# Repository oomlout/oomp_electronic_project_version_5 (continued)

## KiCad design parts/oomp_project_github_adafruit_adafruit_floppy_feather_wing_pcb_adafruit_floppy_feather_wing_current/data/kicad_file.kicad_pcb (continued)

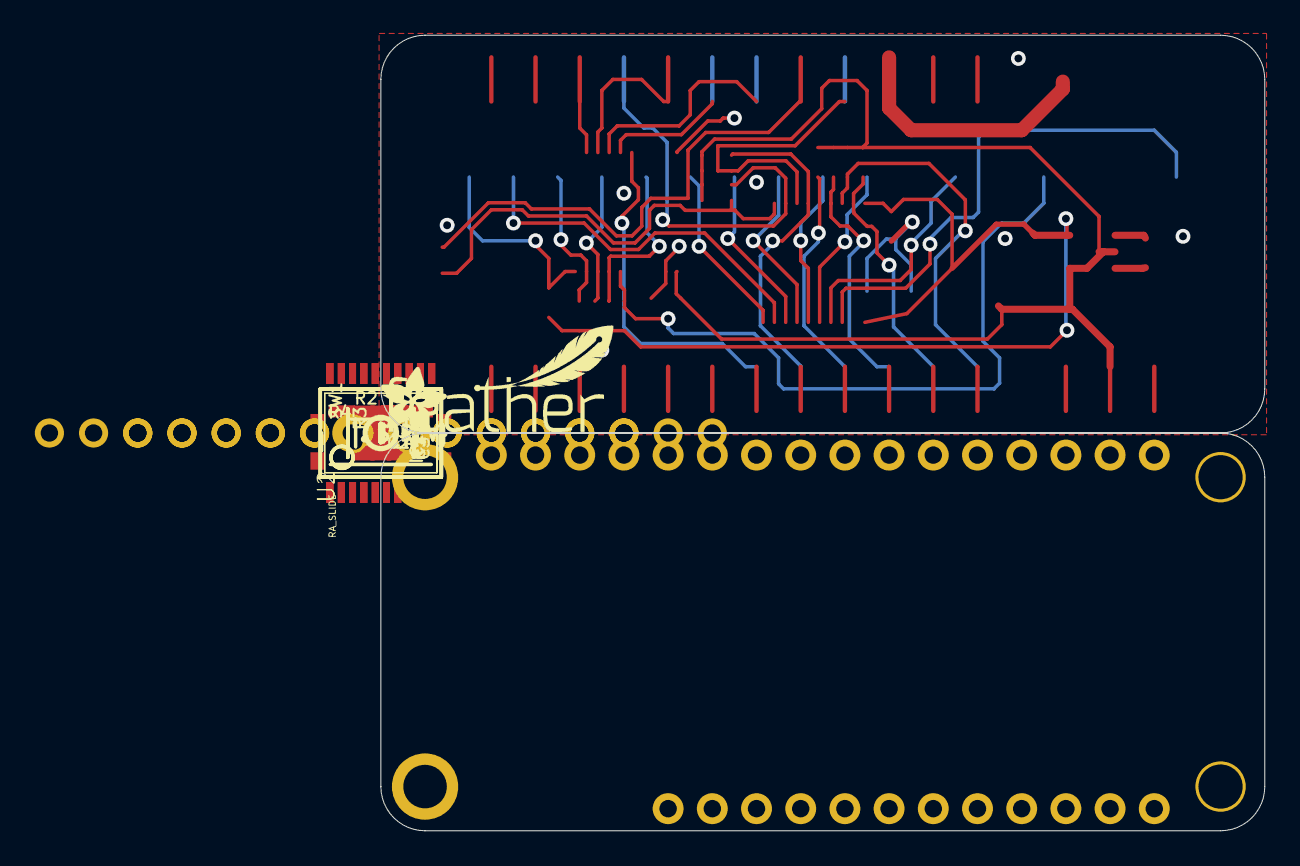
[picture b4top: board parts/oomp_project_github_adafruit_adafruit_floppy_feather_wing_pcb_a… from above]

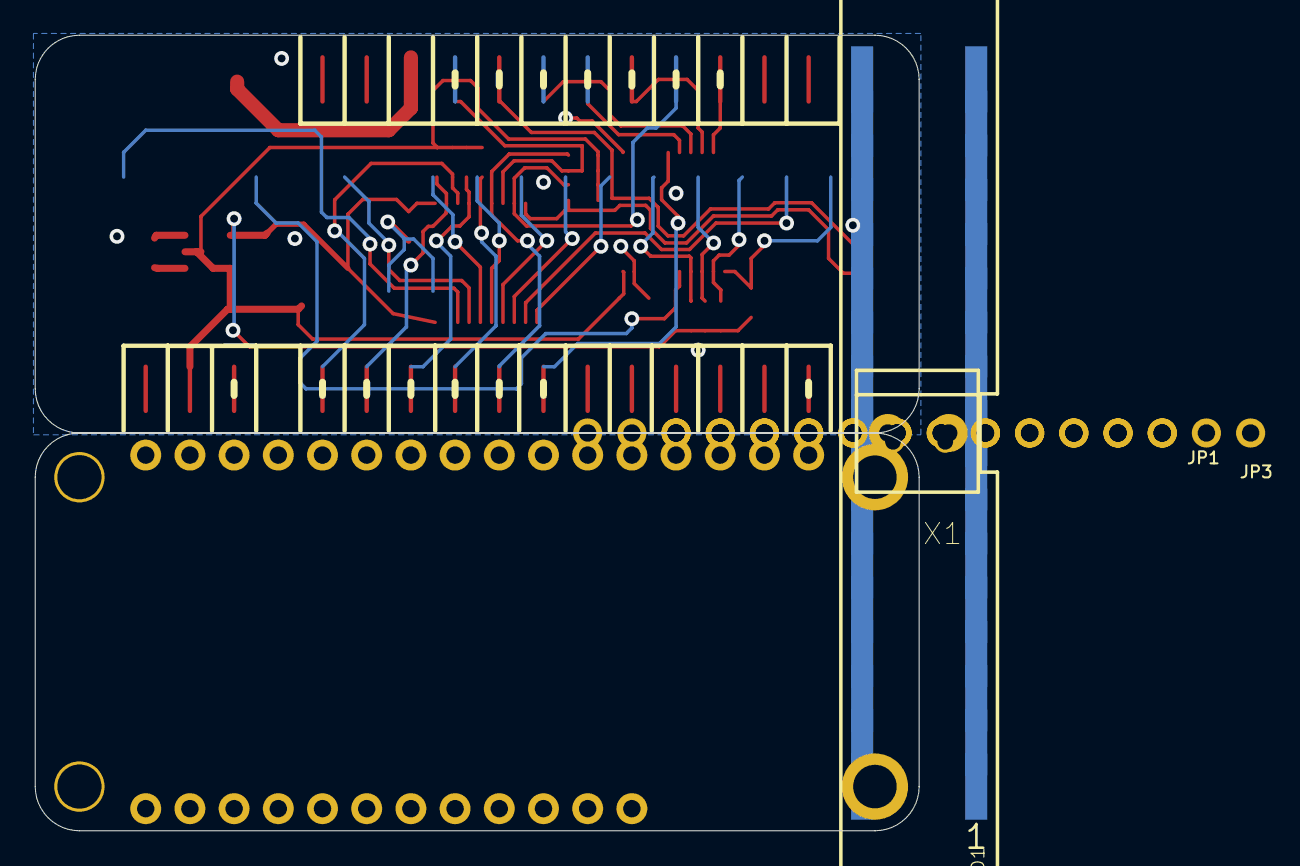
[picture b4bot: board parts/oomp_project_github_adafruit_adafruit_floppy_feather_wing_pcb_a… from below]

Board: 2 copper layers, 50.8 x 45.7 mm, 59 parts (26 on the bottom side), 45 nets.

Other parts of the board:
PLABEL0: PLABEL0
PLABEL1: PLABEL1
PLABEL2: PLABEL2
PLABEL3: PLABEL3
PLABEL4: PLABEL4
PLABEL5: PLABEL5
PLABEL6: PLABEL6
PLABEL7: PLABEL7
PLABEL8: PLABEL8
PLABEL9: PLABEL9
PLABEL10: PLABEL10
PLABEL11: PLABEL11
PLABEL12: PLABEL12
PLABEL13: PLABEL13
PLABEL14: PLABEL14
PLABEL15: PLABEL15
PLABEL16: PLABEL16
PLABEL17: PLABEL17
PLABEL18: PLABEL18
PLABEL19: PLABEL19
PLABEL20: PLABEL20
PLABEL21: PLABEL21
PLABEL22: PLABEL22
PLABEL23: PLABEL23
PLABEL24: PLABEL24
PLABEL25: PLABEL25
PLABEL26: PLABEL26
PLABEL27: PLABEL27
PLABEL28: PLABEL28
PLABEL29: PLABEL29
PLABEL30: PLABEL30
PLABEL31: PLABEL31
PLABEL32: PLABEL32
PLABEL33: PLABEL33
PLABEL34: PLABEL34
PLABEL35: PLABEL35
U$26: PCBFEAT-REV-040
U$27: FEATHERLOGO_SMALL
U$28: ADAFRUIT_3.5MM

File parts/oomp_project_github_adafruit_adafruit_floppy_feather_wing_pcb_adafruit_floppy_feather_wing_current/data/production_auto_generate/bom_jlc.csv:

Comment,Designator,Footprint,LCSC Part #
,JP1,Adafruit Floppy FeatherWing-import-fps:1X12_ROUND,C7501588
,JP3,Adafruit Floppy FeatherWing-import-fps:1X16_ROUND,C7501270
,U$28,Adafruit Floppy FeatherWing-import-fps:ADAFRUIT_3.5MM,
,U$27,Adafruit Floppy FeatherWing-import-fps:FEATHERLOGO_SMALL,
,U$26,Adafruit Floppy FeatherWing-import-fps:PCBFEAT-REV-040,
,PLABEL0,Adafruit Floppy FeatherWing-import-fps:PLABEL0,
,PLABEL1,Adafruit Floppy FeatherWing-import-fps:PLABEL1,
,PLABEL10,Adafruit Floppy FeatherWing-import-fps:PLABEL10,
,PLABEL11,Adafruit Floppy FeatherWing-import-fps:PLABEL11,
,PLABEL12,Adafruit Floppy FeatherWing-import-fps:PLABEL12,
,PLABEL13,Adafruit Floppy FeatherWing-import-fps:PLABEL13,
,PLABEL14,Adafruit Floppy FeatherWing-import-fps:PLABEL14,
,PLABEL15,Adafruit Floppy FeatherWing-import-fps:PLABEL15,
,PLABEL16,Adafruit Floppy FeatherWing-import-fps:PLABEL16,
,PLABEL17,Adafruit Floppy FeatherWing-import-fps:PLABEL17,
,PLABEL18,Adafruit Floppy FeatherWing-import-fps:PLABEL18,
,PLABEL19,Adafruit Floppy FeatherWing-import-fps:PLABEL19,
,PLABEL2,Adafruit Floppy FeatherWing-import-fps:PLABEL2,
,PLABEL20,Adafruit Floppy FeatherWing-import-fps:PLABEL20,
,PLABEL21,Adafruit Floppy FeatherWing-import-fps:PLABEL21,
,PLABEL22,Adafruit Floppy FeatherWing-import-fps:PLABEL22,
,PLABEL23,Adafruit Floppy FeatherWing-import-fps:PLABEL23,
,PLABEL24,Adafruit Floppy FeatherWing-import-fps:PLABEL24,
,PLABEL25,Adafruit Floppy FeatherWing-import-fps:PLABEL25,
,PLABEL26,Adafruit Floppy FeatherWing-import-fps:PLABEL26,
,PLABEL27,Adafruit Floppy FeatherWing-import-fps:PLABEL27,
,PLABEL28,Adafruit Floppy FeatherWing-import-fps:PLABEL28,
,PLABEL29,Adafruit Floppy FeatherWing-import-fps:PLABEL29,
,PLABEL3,Adafruit Floppy FeatherWing-import-fps:PLABEL3,
,PLABEL30,Adafruit Floppy FeatherWing-import-fps:PLABEL30,
,PLABEL31,Adafruit Floppy FeatherWing-import-fps:PLABEL31,
,PLABEL32,Adafruit Floppy FeatherWing-import-fps:PLABEL32,
,PLABEL33,Adafruit Floppy FeatherWing-import-fps:PLABEL33,
,PLABEL34,Adafruit Floppy FeatherWing-import-fps:PLABEL34,
,PLABEL35,Adafruit Floppy FeatherWing-import-fps:PLABEL35,
,PLABEL4,Adafruit Floppy FeatherWing-import-fps:PLABEL4,
,PLABEL5,Adafruit Floppy FeatherWing-import-fps:PLABEL5,
,PLABEL6,Adafruit Floppy FeatherWing-import-fps:PLABEL6,
,PLABEL7,Adafruit Floppy FeatherWing-import-fps:PLABEL7,
,PLABEL8,Adafruit Floppy FeatherWing-import-fps:PLABEL8,
,PLABEL9,Adafruit Floppy FeatherWing-import-fps:PLABEL9,
10uF,"C3,C4",Adafruit Floppy FeatherWing-import-fps:0805-NO,
1uF,"C1,C2,C5",Adafruit Floppy FeatherWing-import-fps:0603-NO,C5673
2.2K,R5,Adafruit Floppy FeatherWing-import-fps:0603-NO,C4190
2.2K pack,"R2,R3,R4",Adafruit Floppy FeatherWing-import-fps:RESPACK_4X0603,C4190
3.5mm,X1,Adafruit Floppy FeatherWing-import-fps:TERMBLOCK_1X2-3.5MM,
74AHCT245,"U1,U2",Adafruit Floppy FeatherWing-import-fps:SSOP20,
AP3602,IC1,Adafruit Floppy FeatherWing-import-fps:SOT23-6,
FEATHERWING,MS1,Adafruit Floppy FeatherWing-import-fps:FEATHERWING,
FLOPPY_IDC_SMT,FDD1,Adafruit Floppy FeatherWing-import-fps:2X17_FLOPPY_SMTIDC,
RA_SLIDE,SW1,Adafruit Floppy FeatherWing-import-fps:SPDT_SMT_SSSS811101,
